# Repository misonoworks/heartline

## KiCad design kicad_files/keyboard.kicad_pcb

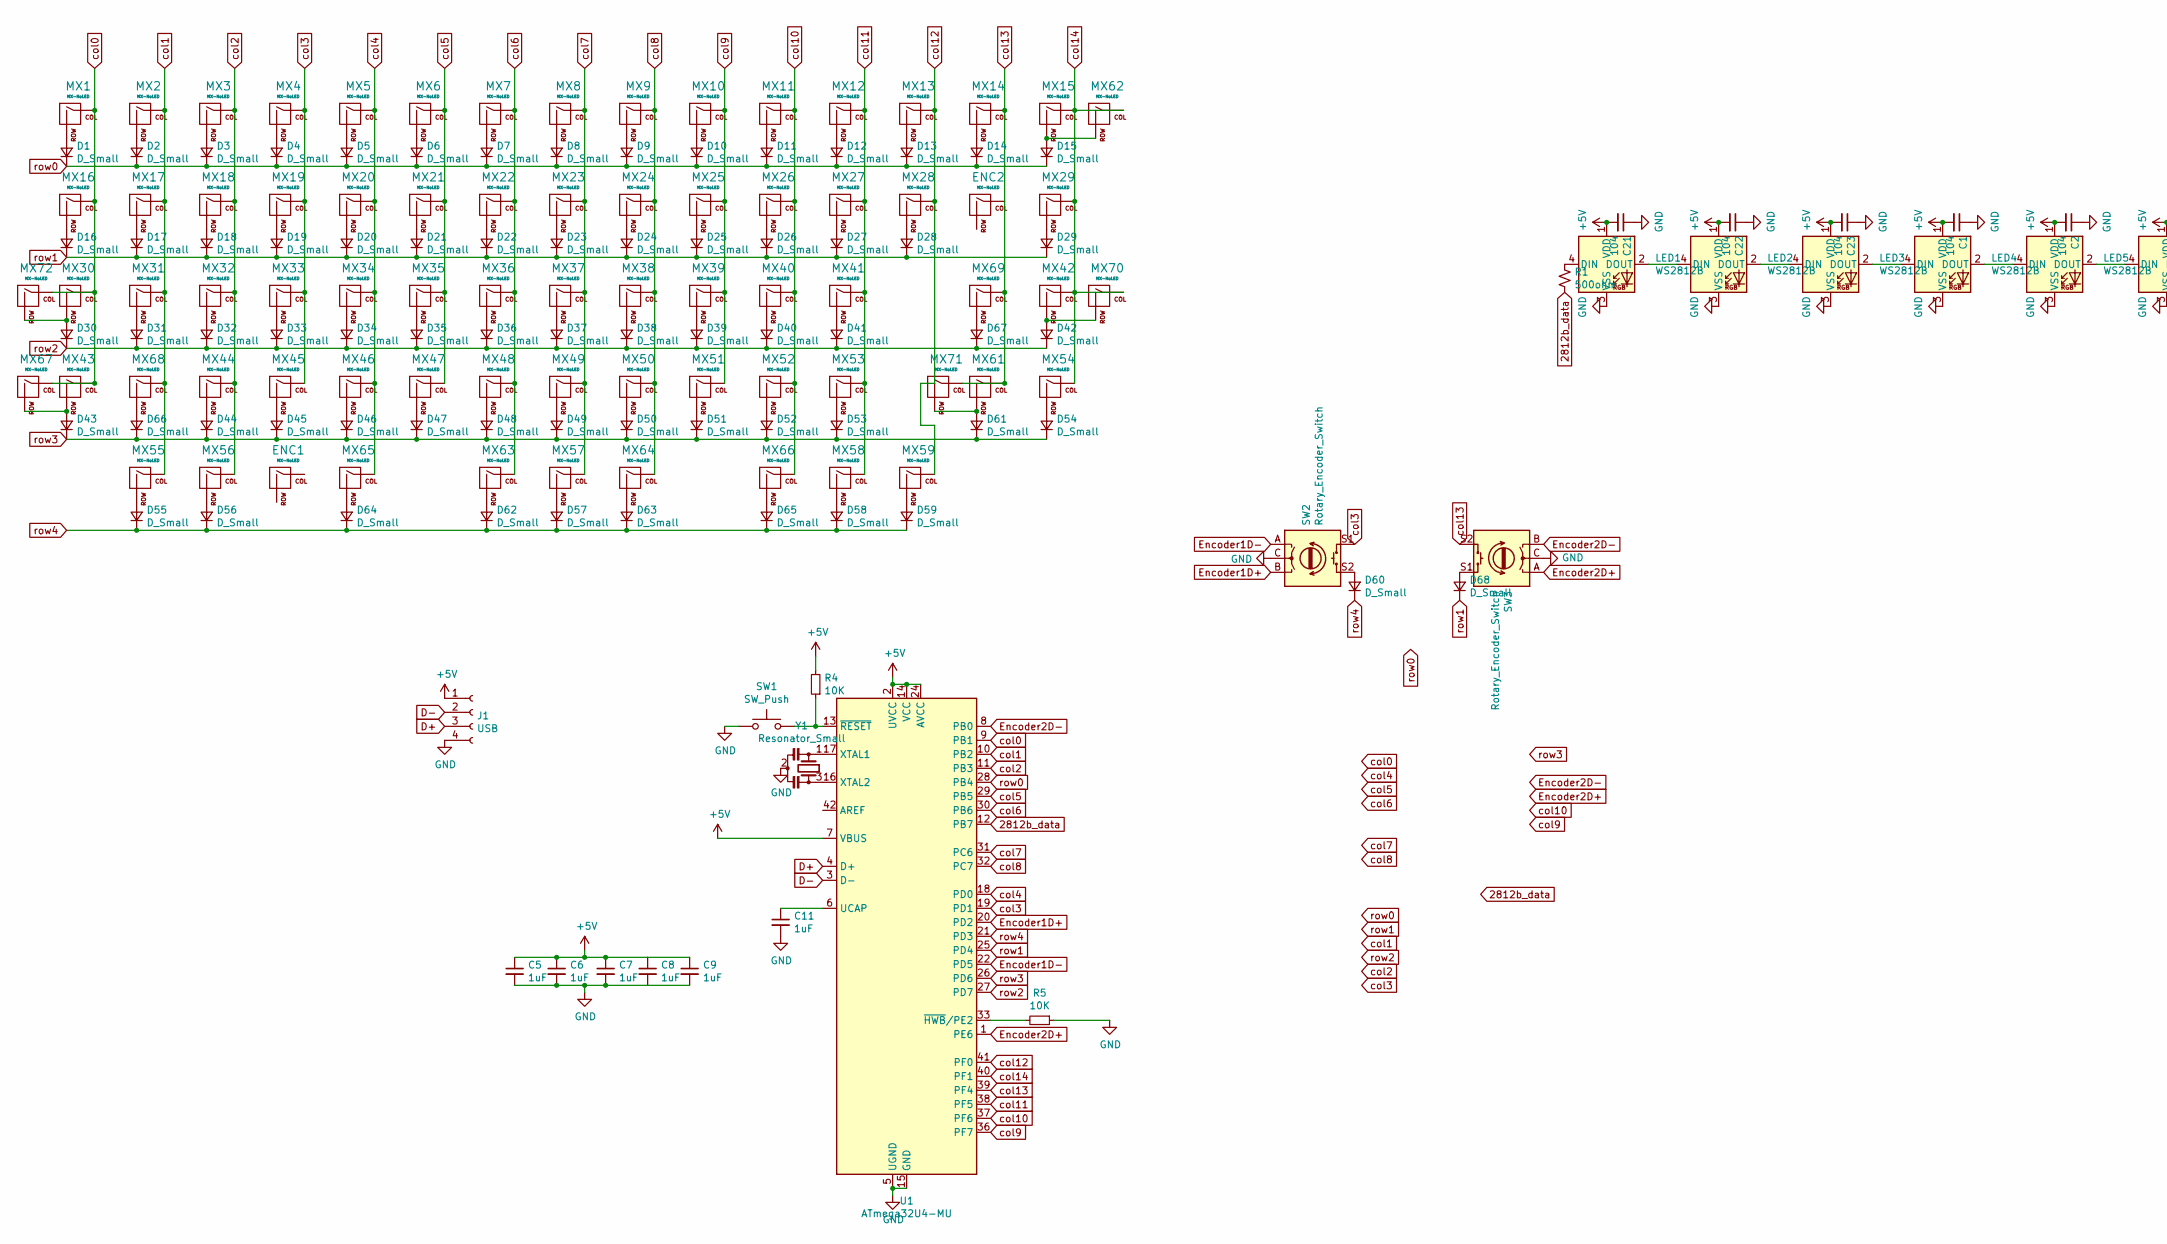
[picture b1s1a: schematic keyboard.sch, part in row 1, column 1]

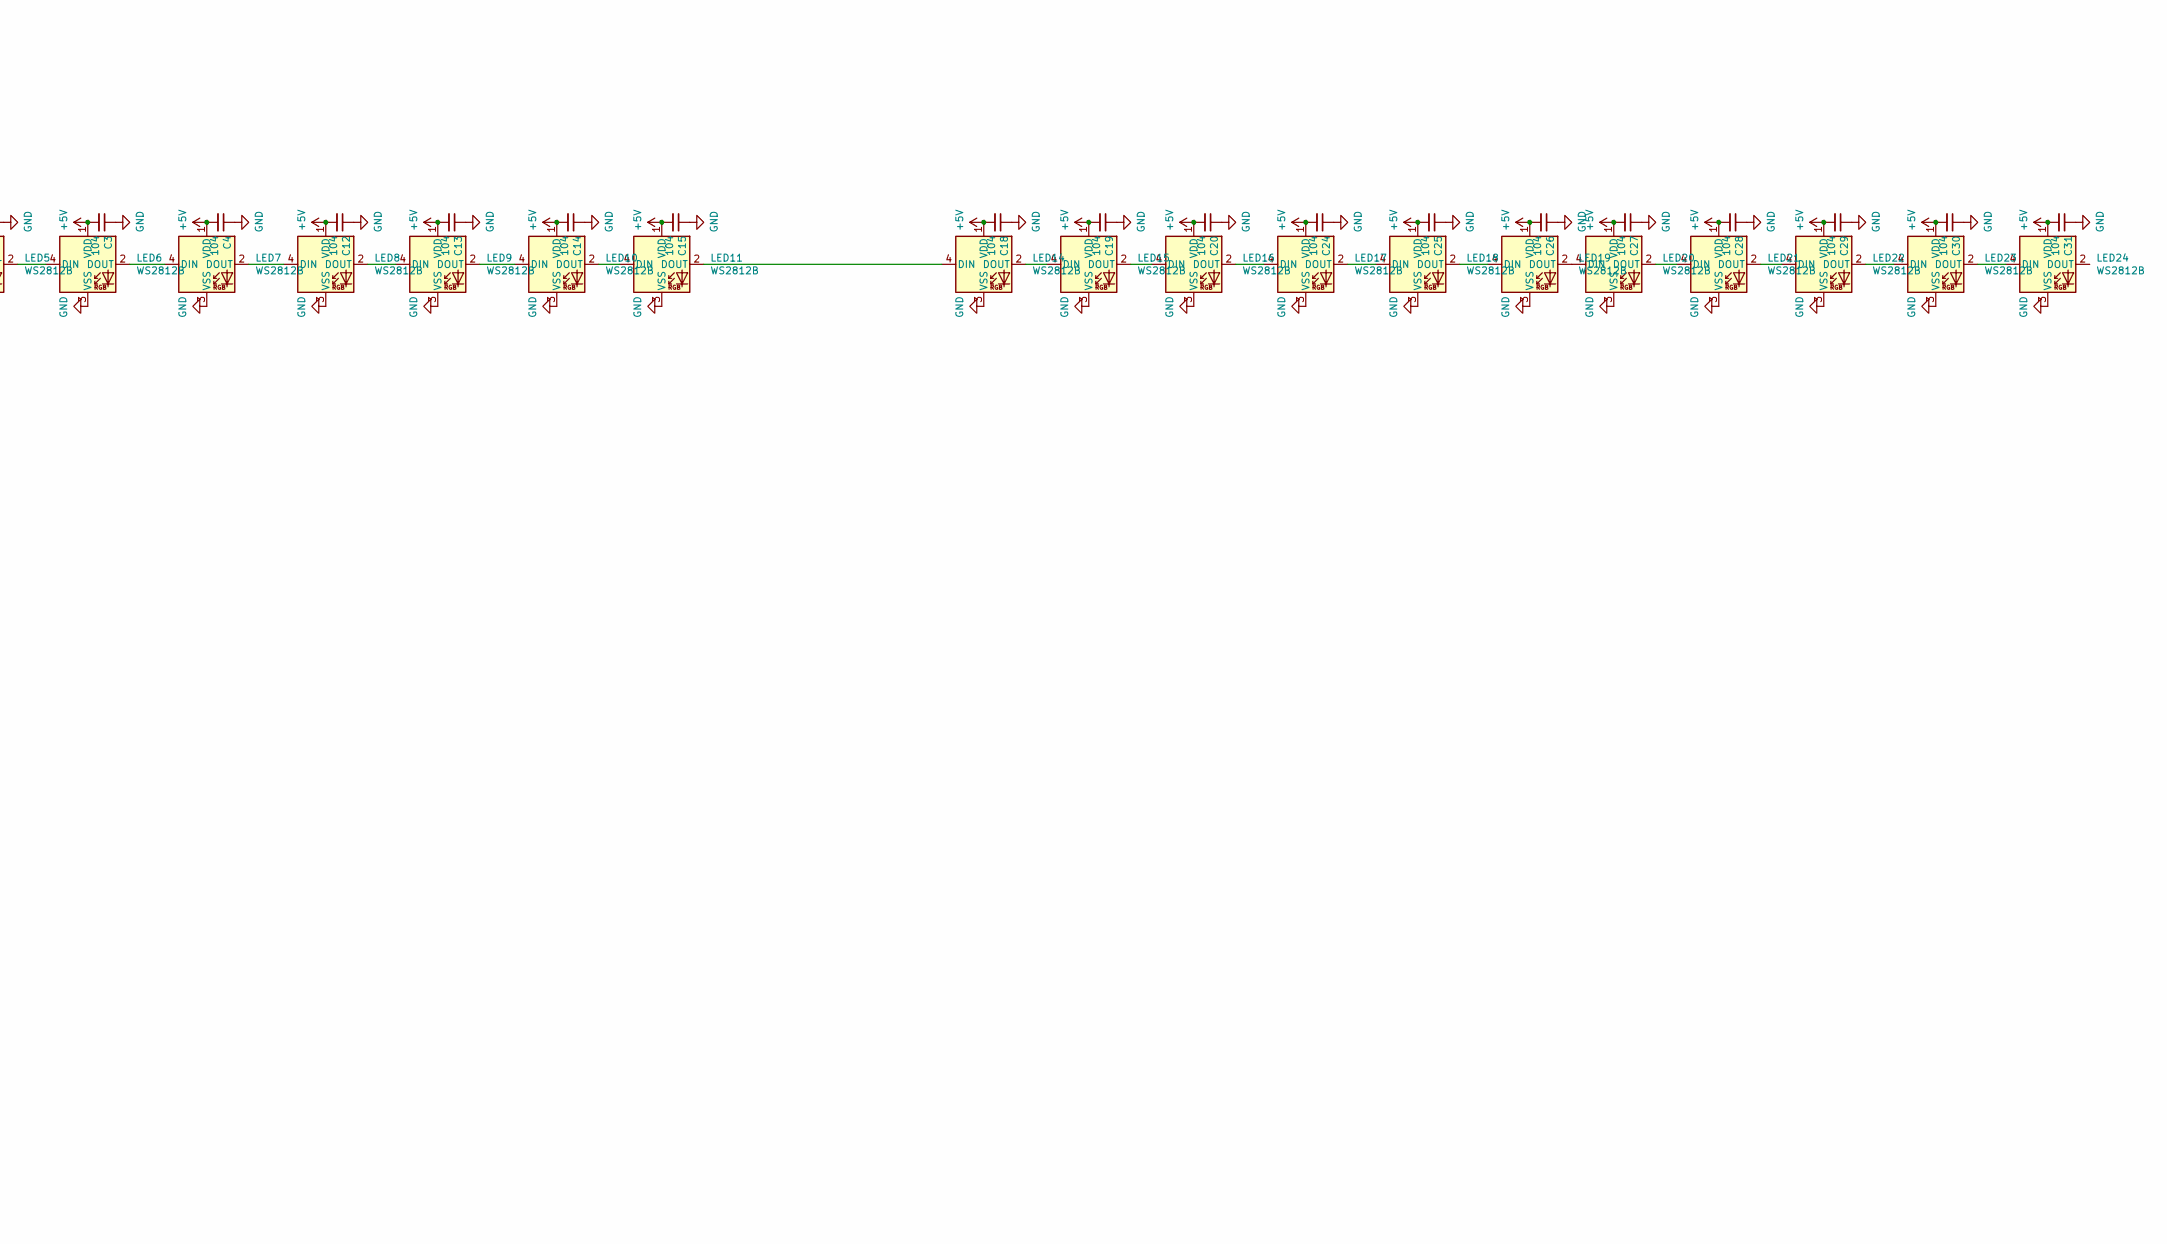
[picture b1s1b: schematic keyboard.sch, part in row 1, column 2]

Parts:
C1, C2, C3, C4, C12, C13, C14, C15, C18, C19, C20, C21, C22, C23, C24, C25, C26, C27, C28, C29, C30, C31: 104; C_0402_1005Metric
C5, C6, C7, C8, C9, C11: 1uF; C_0402_1005Metric
D1, D2, D3, D4, D5, D6, D7, D8, D9, D10, D11, D12, D13, D14, D15, D16, D17, D18, D19, D20, D21, D22, D23, D24, D25, D26, D27, D28, D29, D30, D31, D32, D33, D34, D35, D36, D37, D38, D39, D40, D41, D42, D43, D44, D45, D46, D47, D48, D49, D50, D51, D52, D53, D54, D55, D56, D57, D58, D59, D60, D61, D62, D63, D64, D65, D66, D67, D68: D_Small; D_SOD-123
ENC1, ENC2: MX-NoLED; MXOnly-1U-NoLED
J1: USB; JST_SH_SM04B-SRSS-TB_1x04-1MP_P1.00mm_Horizontal
LED1, LED2, LED3, LED4, LED5, LED6, LED7, LED8, LED9, LED10, LED11, LED14, LED15, LED16, LED17, LED18, LED19, LED20, LED21, LED22, LED23, LED24: WS2812B; LED_WS2812B_PLCC4_5.0x5.0mm_P3.2mm
MX1, MX2, MX3, MX4, MX5, MX6, MX7, MX8, MX9, MX10, MX11, MX12, MX13, MX14, MX15, MX17, MX18, MX19, MX20, MX21, MX22, MX23, MX24, MX25, MX26, MX27, MX28, MX31, MX32, MX33, MX34, MX35, MX36, MX37, MX38, MX39, MX40, MX41, MX44, MX45, MX46, MX47, MX48, MX49, MX50, MX51, MX52, MX53, MX54, MX55, MX59, MX68, MX69: MX-NoLED; MXOnly-1U-NoLED
MX16, MX29, MX56, MX58: MX-NoLED; MXOnly-1.5U-NoLED
MX30, MX61: MX-NoLED; MXOnly-1.75U-NoLED
MX42: MX-NoLED; MXOnly-2.25U-NoLED
MX43: MX-NoLED; MXOnly-2.25U-ReversedStabilizers-NoLED
MX57: MX-NoLED; MX-7U-ReversedStabilizers-NoLED
MX62: MX-NoLED; MXOnly-2U-NoLED
MX63: MX-NoLED; MX-2.75U-ReversedStabilizers-NoLED
MX64: MX-NoLED; MX-2.25U-ReversedStabilizers-NoLED
MX65, MX66: MX-NoLED; MX-1U-NoLED
MX67, MX72: MX-NoLED; MX-1.25U-NoLED
MX70: MX-NoLED; MX-ISO-NoLed
MX71: MX-NoLED; MX-2.75U-NoLED
R1: 500ohm; C_0402_1005Metric
R4, R5: 10K; C_0402_1005Metric
SW1: SW_Push; SKQG-1155865
SW2, SW3: Rotary_Encoder_Switch; RotaryEncoder_Alps_EC12E-Switch_Vertical_H20mm
U1: ATmega32U4-MU; QFN-44-1EP_7x7mm_P0.5mm_EP5.2x5.2mm
Y1: Resonator_Small; Resonator_SMD_muRata_CSTxExxV-3Pin_3.0x1.1mm_HandSoldering

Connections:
2812b_data: R1.2, U1.12 (PB7)
+5V: C1.2, C2.2, C3.2, C4.2, C5.1, C6.1, C7.1, C8.1, C9.1, C12.2, C13.2, C14.2, C15.2, C18.2, C19.2, C20.2, C21.2, C22.2, C23.2, C24.2, C25.2, C26.2, C27.2, C28.2, C29.2, C30.2, C31.2, J1.1, LED1.1 (VDD), LED2.1 (VDD), LED3.1 (VDD), LED4.1 (VDD), LED5.1 (VDD), LED6.1 (VDD), LED7.1 (VDD), LED8.1 (VDD), LED9.1 (VDD), LED10.1 (VDD), LED11.1 (VDD), LED14.1 (VDD), LED15.1 (VDD), LED16.1 (VDD), LED17.1 (VDD), LED18.1 (VDD), LED19.1 (VDD), LED20.1 (VDD), LED21.1 (VDD), LED22.1 (VDD), LED23.1 (VDD), LED24.1 (VDD), R4.2, U1.2 (UVCC), U1.7 (VBUS), U1.14 (VCC), U1.24 (AVCC), U1.34 (VCC), U1.44 (AVCC)
D+: J1.3, U1.4 (D+)
D-: J1.2, U1.3 (D-)
Encoder1D+: SW2.B, U1.20 (PD2)
Encoder1D-: SW2.A, U1.22 (PD5)
Encoder2D+: SW3.A, U1.1 (PE6)
Encoder2D-: SW3.B, U1.8 (PB0)
GND: C1.1, C2.1, C3.1, C4.1, C5.2, C6.2, C7.2, C8.2, C9.2, C11.2, C12.1, C13.1, C14.1, C15.1, C18.1, C19.1, C20.1, C21.1, C22.1, C23.1, C24.1, C25.1, C26.1, C27.1, C28.1, C29.1, C30.1, C31.1, J1.4, LED1.3 (VSS), LED2.3 (VSS), LED3.3 (VSS), LED4.3 (VSS), LED5.3 (VSS), LED6.3 (VSS), LED7.3 (VSS), LED8.3 (VSS), LED9.3 (VSS), LED10.3 (VSS), LED11.3 (VSS), LED14.3 (VSS), LED15.3 (VSS), LED16.3 (VSS), LED17.3 (VSS), LED18.3 (VSS), LED19.3 (VSS), LED20.3 (VSS), LED21.3 (VSS), LED22.3 (VSS), LED23.3 (VSS), LED24.3 (VSS), R5.1, SW1.1, SW2.C, SW3.C, U1.5 (UGND), U1.15 (GND), U1.23 (GND), U1.35 (GND), U1.43 (GND), U1.45 (GND), Y1.2
unnamed: C11.1, U1.6 (UCAP)
unnamed: D1.2 (A), MX1.2 (ROW)
unnamed: D2.2 (A), MX2.2 (ROW)
unnamed: D3.2 (A), MX3.2 (ROW)
unnamed: D4.2 (A), MX4.2 (ROW)
unnamed: D5.2 (A), MX5.2 (ROW)
unnamed: D6.2 (A), MX6.2 (ROW)
unnamed: D7.2 (A), MX7.2 (ROW)
unnamed: D8.2 (A), MX8.2 (ROW)
unnamed: D9.2 (A), MX9.2 (ROW)
unnamed: D10.2 (A), MX10.2 (ROW)
unnamed: D11.2 (A), MX11.2 (ROW)
unnamed: D12.2 (A), MX12.2 (ROW)
unnamed: D13.2 (A), MX13.2 (ROW)
unnamed: D14.2 (A), MX14.2 (ROW)
unnamed: D15.2 (A), MX15.2 (ROW), MX62.2 (ROW)
unnamed: D16.2 (A), MX16.2 (ROW)
unnamed: D17.2 (A), MX17.2 (ROW)
unnamed: D18.2 (A), MX18.2 (ROW)
unnamed: D19.2 (A), MX19.2 (ROW)
unnamed: D20.2 (A), MX20.2 (ROW)
unnamed: D21.2 (A), MX21.2 (ROW)
unnamed: D22.2 (A), MX22.2 (ROW)
unnamed: D23.2 (A), MX23.2 (ROW)
unnamed: D24.2 (A), MX24.2 (ROW)
unnamed: D25.2 (A), MX25.2 (ROW)
unnamed: D26.2 (A), MX26.2 (ROW)
unnamed: D27.2 (A), MX27.2 (ROW)
unnamed: D28.2 (A), MX28.2 (ROW)
unnamed: D29.2 (A), MX29.2 (ROW)
unnamed: D30.2 (A), MX30.2 (ROW), MX72.2 (ROW)
unnamed: D31.2 (A), MX31.2 (ROW)
unnamed: D32.2 (A), MX32.2 (ROW)
unnamed: D33.2 (A), MX33.2 (ROW)
unnamed: D34.2 (A), MX34.2 (ROW)
unnamed: D35.2 (A), MX35.2 (ROW)
unnamed: D36.2 (A), MX36.2 (ROW)
unnamed: D37.2 (A), MX37.2 (ROW)
unnamed: D38.2 (A), MX38.2 (ROW)
unnamed: D39.2 (A), MX39.2 (ROW)
unnamed: D40.2 (A), MX40.2 (ROW)
unnamed: D41.2 (A), MX41.2 (ROW)
unnamed: D42.2 (A), MX42.2 (ROW), MX70.2 (ROW)
unnamed: D43.2 (A), MX43.2 (ROW), MX67.2 (ROW)
unnamed: D44.2 (A), MX44.2 (ROW)
unnamed: D45.2 (A), MX45.2 (ROW)
unnamed: D46.2 (A), MX46.2 (ROW)
unnamed: D47.2 (A), MX47.2 (ROW)
unnamed: D48.2 (A), MX48.2 (ROW)
unnamed: D49.2 (A), MX49.2 (ROW)
unnamed: D50.2 (A), MX50.2 (ROW)
unnamed: D51.2 (A), MX51.2 (ROW)
unnamed: D52.2 (A), MX52.2 (ROW)
unnamed: D53.2 (A), MX53.2 (ROW)
unnamed: D54.2 (A), MX54.2 (ROW)
unnamed: D55.2 (A), MX55.2 (ROW)
unnamed: D56.2 (A), MX56.2 (ROW)
unnamed: D57.2 (A), MX57.2 (ROW)
unnamed: D58.2 (A), MX58.2 (ROW)
unnamed: D59.2 (A), MX59.2 (ROW)
unnamed: D60.2 (A), SW2.S2
unnamed: D61.2 (A), MX61.2 (ROW), MX71.2 (ROW)
unnamed: D62.2 (A), MX63.2 (ROW)
unnamed: D63.2 (A), MX64.2 (ROW)
unnamed: D64.2 (A), MX65.2 (ROW)
unnamed: D65.2 (A), MX66.2 (ROW)
unnamed: D66.2 (A), MX68.2 (ROW)
unnamed: D67.2 (A), MX69.2 (ROW)
unnamed: D68.2 (A), SW3.S1
unnamed: LED1.2 (DOUT), LED2.4 (DIN)
unnamed: LED1.4 (DIN), R1.1
unnamed: LED2.2 (DOUT), LED3.4 (DIN)
unnamed: LED3.2 (DOUT), LED4.4 (DIN)
unnamed: LED4.2 (DOUT), LED5.4 (DIN)
unnamed: LED5.2 (DOUT), LED6.4 (DIN)
unnamed: LED6.2 (DOUT), LED7.4 (DIN)
unnamed: LED7.2 (DOUT), LED8.4 (DIN)
unnamed: LED8.2 (DOUT), LED9.4 (DIN)
unnamed: LED10.2 (DOUT), LED11.4 (DIN)
unnamed: LED9.2 (DOUT), LED10.4 (DIN)
unnamed: LED11.2 (DOUT), LED14.4 (DIN)
unnamed: LED14.2 (DOUT), LED15.4 (DIN)
unnamed: LED15.2 (DOUT), LED16.4 (DIN)
unnamed: LED16.2 (DOUT), LED17.4 (DIN)
unnamed: LED17.2 (DOUT), LED18.4 (DIN)
unnamed: LED18.2 (DOUT), LED19.4 (DIN)
unnamed: LED19.2 (DOUT), LED20.4 (DIN)
unnamed: LED20.2 (DOUT), LED21.4 (DIN)
unnamed: LED21.2 (DOUT), LED22.4 (DIN)
unnamed: LED22.2 (DOUT), LED23.4 (DIN)
unnamed: LED23.2 (DOUT), LED24.4 (DIN)
unnamed: R4.1, SW1.2, U1.13 (~RESET)
unnamed: R5.2, U1.33 (~HWB~/PE2)
unnamed: U1.16 (XTAL2), Y1.3
unnamed: U1.17 (XTAL1), Y1.1
col0: MX1.1 (COL), MX16.1 (COL), MX30.1 (COL), MX43.1 (COL), MX67.1 (COL), MX72.1 (COL), U1.9 (PB1)
col1: MX2.1 (COL), MX17.1 (COL), MX31.1 (COL), MX55.1 (COL), MX68.1 (COL), U1.10 (PB2)
col2: MX3.1 (COL), MX18.1 (COL), MX32.1 (COL), MX44.1 (COL), MX56.1 (COL), U1.11 (PB3)
col3: MX4.1 (COL), MX19.1 (COL), MX33.1 (COL), MX45.1 (COL), SW2.S1, U1.19 (PD1)
col4: MX5.1 (COL), MX20.1 (COL), MX34.1 (COL), MX46.1 (COL), MX65.1 (COL), U1.18 (PD0)
col5: MX6.1 (COL), MX21.1 (COL), MX35.1 (COL), MX47.1 (COL), U1.29 (PB5)
col6: MX7.1 (COL), MX22.1 (COL), MX36.1 (COL), MX48.1 (COL), MX63.1 (COL), U1.30 (PB6)
col7: MX8.1 (COL), MX23.1 (COL), MX37.1 (COL), MX49.1 (COL), MX57.1 (COL), U1.31 (PC6)
col8: MX9.1 (COL), MX24.1 (COL), MX38.1 (COL), MX50.1 (COL), MX64.1 (COL), U1.32 (PC7)
col9: MX10.1 (COL), MX25.1 (COL), MX39.1 (COL), MX51.1 (COL), U1.36 (PF7)
col10: MX11.1 (COL), MX26.1 (COL), MX40.1 (COL), MX52.1 (COL), MX66.1 (COL), U1.37 (PF6)
col11: MX12.1 (COL), MX27.1 (COL), MX41.1 (COL), MX53.1 (COL), MX58.1 (COL), U1.38 (PF5)
col12: MX13.1 (COL), MX28.1 (COL), MX59.1 (COL), U1.41 (PF0)
col13: MX14.1 (COL), MX61.1 (COL), MX69.1 (COL), MX71.1 (COL), SW3.S2, U1.39 (PF4)
col14: MX15.1 (COL), MX29.1 (COL), MX42.1 (COL), MX54.1 (COL), MX62.1 (COL), MX70.1 (COL), U1.40 (PF1)
row0: D1.1 (K), D2.1 (K), D3.1 (K), D4.1 (K), D5.1 (K), D6.1 (K), D7.1 (K), D8.1 (K), D9.1 (K), D10.1 (K), D11.1 (K), D12.1 (K), D13.1 (K), D14.1 (K), D15.1 (K), U1.28 (PB4)
row1: D16.1 (K), D17.1 (K), D18.1 (K), D19.1 (K), D20.1 (K), D21.1 (K), D22.1 (K), D23.1 (K), D24.1 (K), D25.1 (K), D26.1 (K), D27.1 (K), D28.1 (K), D29.1 (K), D68.1 (K), U1.25 (PD4)
row2: D30.1 (K), D31.1 (K), D32.1 (K), D33.1 (K), D34.1 (K), D35.1 (K), D36.1 (K), D37.1 (K), D38.1 (K), D39.1 (K), D40.1 (K), D41.1 (K), D42.1 (K), D67.1 (K), U1.27 (PD7)
row3: D43.1 (K), D44.1 (K), D45.1 (K), D46.1 (K), D47.1 (K), D48.1 (K), D49.1 (K), D50.1 (K), D51.1 (K), D52.1 (K), D53.1 (K), D54.1 (K), D61.1 (K), D66.1 (K), U1.26 (PD6)
row4: D55.1 (K), D56.1 (K), D57.1 (K), D58.1 (K), D59.1 (K), D60.1 (K), D62.1 (K), D63.1 (K), D64.1 (K), D65.1 (K), U1.21 (PD3)

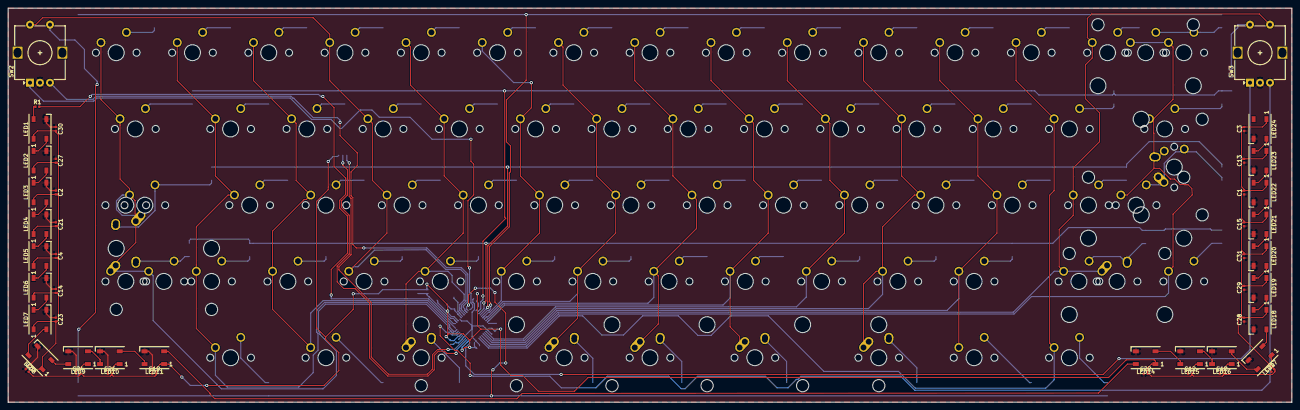
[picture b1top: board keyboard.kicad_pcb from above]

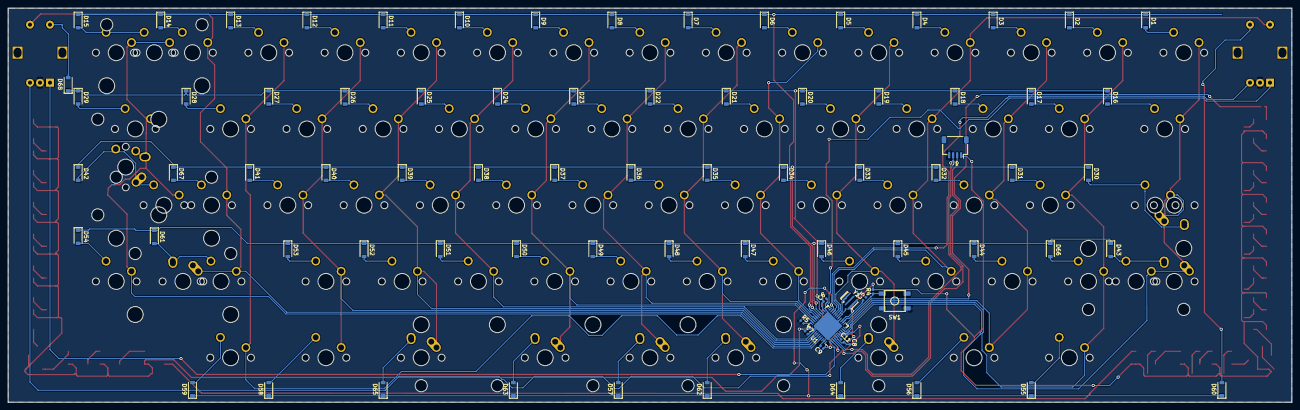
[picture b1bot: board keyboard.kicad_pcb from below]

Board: 2 copper layers, 320.7 x 98.4 mm, 198 parts (80 on the bottom side), 124 nets.

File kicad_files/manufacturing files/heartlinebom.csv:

Comment,Designator,Footprint,LCSC
"1uF","C11,C5,C6,C7,C8,C9","Capacitor_SMD:C_0402_1005Metric",""
"104","C3,C2,C1,C4,C12,C13,C14,C18,C19,C20,C23,C24,C22,C25,C26,C21,C27,C28,C29,C30,C31,C15","Capacitor_SMD:C_0402_1005Metric",""
"D_Small","D1,D2,D3,D4,D5,D6,D7,D8,D9,D10,D11,D12,D13,D14,D15,D16,D17,D18,D19,D20,D21,D22,D23,D24,D25,D26,D27,D28,D29,D30,D31,D32,D33,D34,D35,D36,D37,D38,D39,D40,D41,D42,D43,D44,D45,D46,D47,D48,D49,D50,D51,D52,D53,D54,D55,D56,D57,D58,D59,D61,D63,D62,D65,D64,D66,D67,D60,D68","Diode_SMD:D_SOD-123",""
"USB","J1","Connector_JST:JST_SH_SM04B-SRSS-TB_1x04-1MP_P1.00mm_Horizontal",""
"WS2812B","LED6,LED5,LED4,LED7,LED8,LED9,LED10,LED14,LED15,LED16,LED3,LED17,LED2,LED18,LED19,LED1,LED20,LED21,LED22,LED23,LED24,LED11","LED_SMD:LED_WS2812B_PLCC4_5.0x5.0mm_P3.2mm",""
"MX-NoLED","MX1,MX2,MX3,MX4,MX5,MX6,MX7,MX8,MX9,MX10,MX11,MX12,MX13,MX14,MX15,MX17,MX18,MX19,MX20,MX21,MX22,MX23,MX24,MX25,MX26,MX27,MX28,MX31,MX32,MX33,MX34,MX35,MX36,MX37,MX38,MX39,MX40,MX41,MX44,MX45,MX46,MX47,MX48,MX49,MX50,MX51,MX52,MX53,MX54,MX55,MX59,MX68,MX69","MX_Only:MXOnly-1U-NoLED",""
"MX-NoLED","MX16,MX29,MX56,MX58","MX_Only:MXOnly-1.5U-NoLED",""
"MX-NoLED","MX30,MX61","MX_Only:MXOnly-1.75U-NoLED",""
"MX-NoLED","MX42","MX_Only:MXOnly-2.25U-NoLED",""
"MX-NoLED","MX43","MX_Only:MXOnly-2.25U-ReversedStabilizers-NoLED",""
"MX-NoLED","MX57","MX_Alps_Hybrid:MX-7U-ReversedStabilizers-NoLED",""
"MX-NoLED","MX62","MX_Only:MXOnly-2U-NoLED",""
"MX-NoLED","MX63","MX_Alps_Hybrid:MX-2.75U-ReversedStabilizers-NoLED",""
"MX-NoLED","MX64","MX_Alps_Hybrid:MX-2.25U-ReversedStabilizers-NoLED",""
"MX-NoLED","MX66,MX65","MX_Alps_Hybrid:MX-1U-NoLED",""
"MX-NoLED","MX67,MX72","MX_Alps_Hybrid:MX-1.25U-NoLED",""
"MX-NoLED","MX70","MX_Alps_Hybrid:MX-ISO-NoLed",""
"MX-NoLED","MX71","MX_Alps_Hybrid:MX-2.75U-NoLED",""
"500ohm","R1","Capacitor_SMD:C_0402_1005Metric",""
"10K","R5,R4","Capacitor_SMD:C_0402_1005Metric",""
"SW_Push","SW1","random-keyboard-parts:SKQG-1155865",""
"Rotary_Encoder_Switch","SW3,SW2","Rotary_Encoder:RotaryEncoder_Alps_EC12E-Switch_Vertical_H20mm",""
"ATmega32U4-MU","U1","Package_DFN_QFN:QFN-44-1EP_7x7mm_P0.5mm_EP5.2x5.2mm",""
"Resonator_Small","Y1","Crystal:Resonator_SMD_muRata_CSTxExxV-3Pin_3.0x1.1mm_HandSoldering",""
